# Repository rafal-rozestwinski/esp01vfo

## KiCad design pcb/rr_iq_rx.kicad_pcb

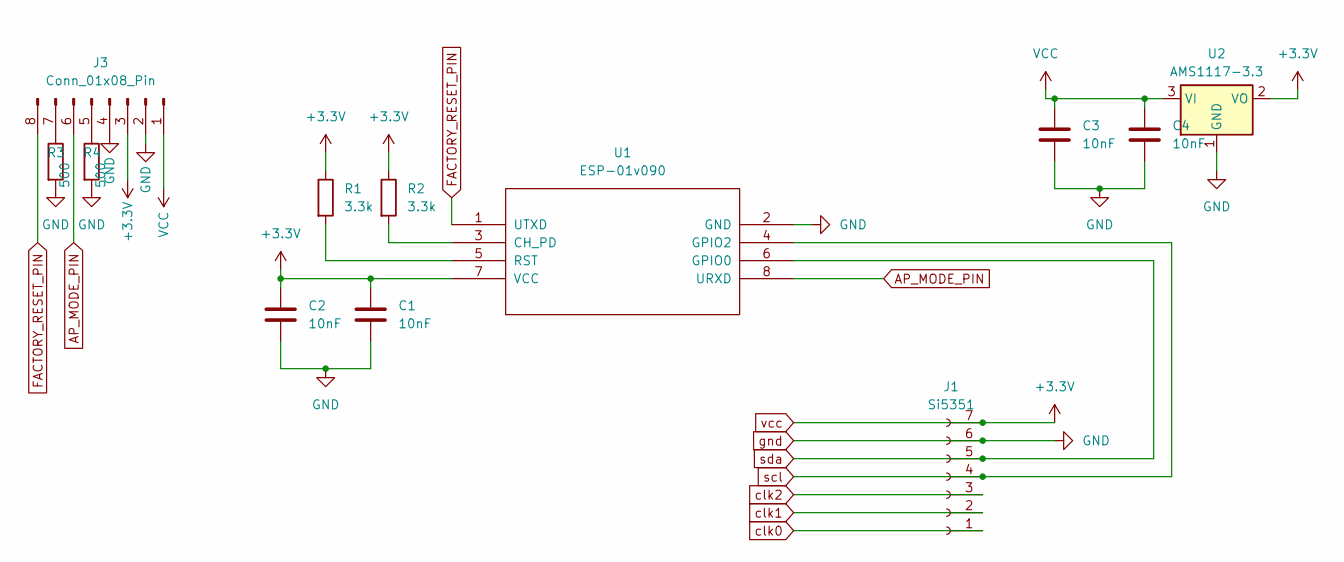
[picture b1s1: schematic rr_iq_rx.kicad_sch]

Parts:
C1, C2, C3, C4: 10nF; C_1206_3216Metric_Pad1.33x1.80mm_HandSolder
J1: Si5351; SI5351 Module
J3: Conn_01x08_Pin; PinHeader_1x08_P2.54mm_Vertical
R1, R2: 3.3k; R_0805_2012Metric_Pad1.20x1.40mm_HandSolder
R3, R4: 500; R_0805_2012Metric_Pad1.20x1.40mm_HandSolder
U1: ESP-01v090; ESP-01
U2: AMS1117-3.3; SOT-223-3_TabPin2

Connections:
AP_MODE_PIN: J3.6, U1.8 (URXD)
FACTORY_RESET_PIN: J3.8, U1.1 (UTXD)
unnamed: J3.5, R4.1
unnamed: J3.7, R3.1
unnamed: R2.2, U1.3 (CH_PD)
unnamed: R1.2, U1.5 (RST)
VCC: C3.2, C4.1, J3.1, U2.3 (VI)
clk0: J1.1
clk1: J1.2
clk2: J1.3
gnd: C1.2, C2.1, C3.1, C4.2, J1.6, J3.2, J3.4, R3.2, R4.2, U1.2 (GND), U2.1 (GND)
scl: J1.4, U1.4 (GPIO2)
sda: J1.5, U1.6 (GPIO0)
vcc: C1.1, C2.2, J1.7, J3.3, R1.1, R2.1, U1.7 (VCC), U2.2 (VO)

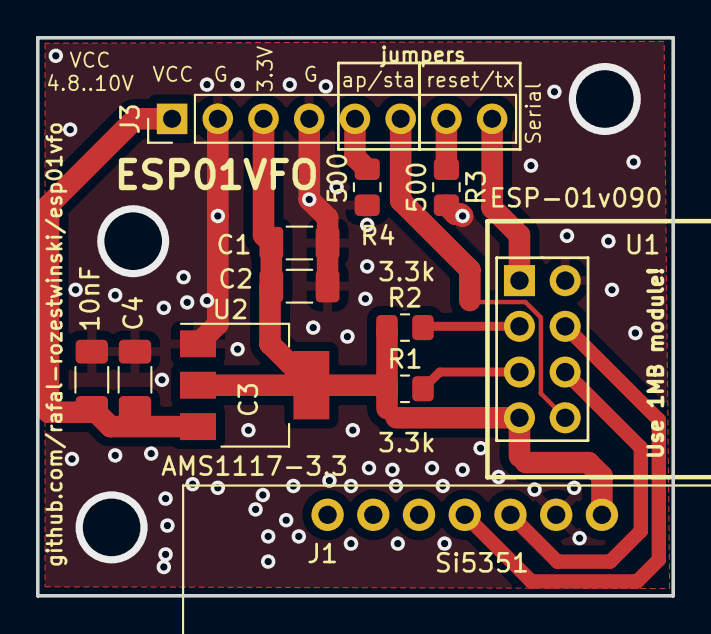
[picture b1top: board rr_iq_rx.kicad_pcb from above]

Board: 2 copper layers, 35.3 x 31.0 mm, 12 parts (0 on the bottom side), 11 nets.

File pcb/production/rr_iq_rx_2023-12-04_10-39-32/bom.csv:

Designator,Footprint,Quantity,Value,LCSC Part #
"C1, C2, C3, C4",1206,4,10nF,
J1,SI5351 Module,1,Si5351,
J2,PinHeader_1x04_P2.54mm_Vertical,1,Conn_01x04_Pin,
"R1, R2",0805,2,3.3k,
U1,ESP-01,1,ESP-01v090,
U2,SOT-223-3_TabPin2,1,AMS1117-3.3,

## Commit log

2023-12-21 Initial
